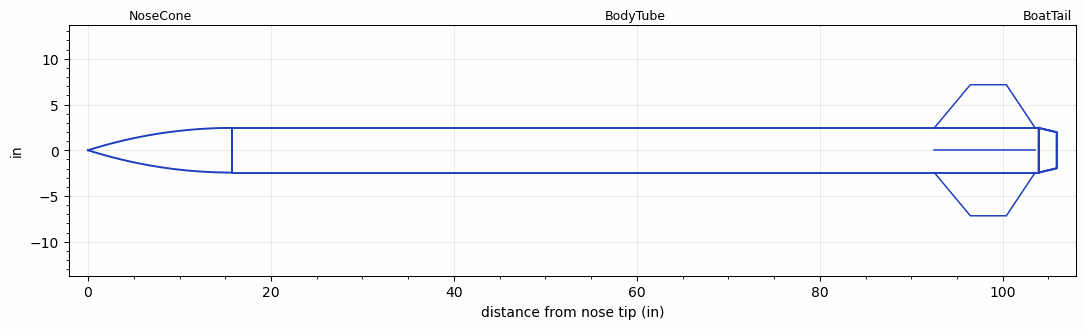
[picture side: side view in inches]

<RASAeroDocument>
 <FileVersion>2</FileVersion>
 <RocketDesign>
  <NoseCone>
   <Length>15.748</Length>
   <Diameter>4.882</Diameter>
   <Shape>Tangent Ogive</Shape>
   <Location>0</Location>
  </NoseCone>
  <BodyTube>
   <Length>88.189</Length>
   <Diameter>4.882</Diameter>
   <RailGuideDiameter>0.63</RailGuideDiameter>
   <RailGuideHeight>0.44</RailGuideHeight>
   <Location>15.748</Location>
   <BoattailLength>1.969</BoattailLength>
   <BoattailRearDiameter>3.937</BoattailRearDiameter>
   <Fin>
    <Count>4</Count>
    <Chord>11.024</Chord>
    <Span>4.724</Span>
    <SweepDistance>3.937</SweepDistance>
    <TipChord>3.937</TipChord>
    <Thickness>0.118</Thickness>
    <Location>11.418</Location>
    <AirfoilSection>Square</AirfoilSection>
   </Fin>
  </BodyTube>
  <BoatTail>
   <Length>1.969</Length>
   <Diameter>4.882</Diameter>
   <RearDiameter>3.937</RearDiameter>
   <Location>103.937</Location>
  </BoatTail>
  <Surface>Rough Camouflage Paint</Surface>
  <ModifiedBarrowman>True</ModifiedBarrowman>
  <Turbulence>True</Turbulence>
  <UseBooster1>False</UseBooster1>
  <UseBooster2>False</UseBooster2>
 </RocketDesign>
 <LaunchSite>
  <Altitude>4596</Altitude>
  <Pressure>0</Pressure>
  <RodAngle>5</RodAngle>
  <RodLength>17</RodLength>
  <Temperature>74</Temperature>
  <WindSpeed>13.4</WindSpeed>
 </LaunchSite>
 <Recovery>
  <Altitude1>1000</Altitude1>
  <Altitude2>1500</Altitude2>
  <DeviceType1>Parachute</DeviceType1>
  <DeviceType2>Parachute</DeviceType2>
  <Event1>True</Event1>
  <Event2>True</Event2>
  <Size1>24</Size1>
  <Size2>84</Size2>
  <EventType1>Apogee</EventType1>
  <EventType2>Altitude</EventType2>
  <CD1>1.3</CD1>
  <CD2>2.2</CD2>
 </Recovery>
 <SimulationList>
  <Simulation>
   <SustainerEngine>L1545  (FURY)</SustainerEngine>
   <SustainerLaunchWt>44.32</SustainerLaunchWt>
   <SustainerNozzleDiameter>2.2047</SustainerNozzleDiameter>
   <SustainerCG>64.96</SustainerCG>
   <SustainerIgnitionDelay>0</SustainerIgnitionDelay>
   <Booster1SeparationDelay>0</Booster1SeparationDelay>
   <Booster1IgnitionDelay>0</Booster1IgnitionDelay>
   <IncludeBooster1>False</IncludeBooster1>
   <Booster2Delay>0</Booster2Delay>
   <IncludeBooster2>False</IncludeBooster2>
   <TimetoApogee>15.45026</TimetoApogee>
   <MaxAltitude>3619.466</MaxAltitude>
   <MaxVelocity>518.7138</MaxVelocity>
   <OptimumWt>21.606</OptimumWt>
   <OptimumMaxAlt>21.606</OptimumMaxAlt>
  </Simulation>
 </SimulationList>
</RASAeroDocument>
